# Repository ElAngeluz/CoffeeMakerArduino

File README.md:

# CoffeeMakerArduino
Hackear una cafetera simple para que se pueda conectar a Internet y de tal forma poder controlarla remotamente. Además la cafetera puede reportar su estado mediante una aplicacion android.

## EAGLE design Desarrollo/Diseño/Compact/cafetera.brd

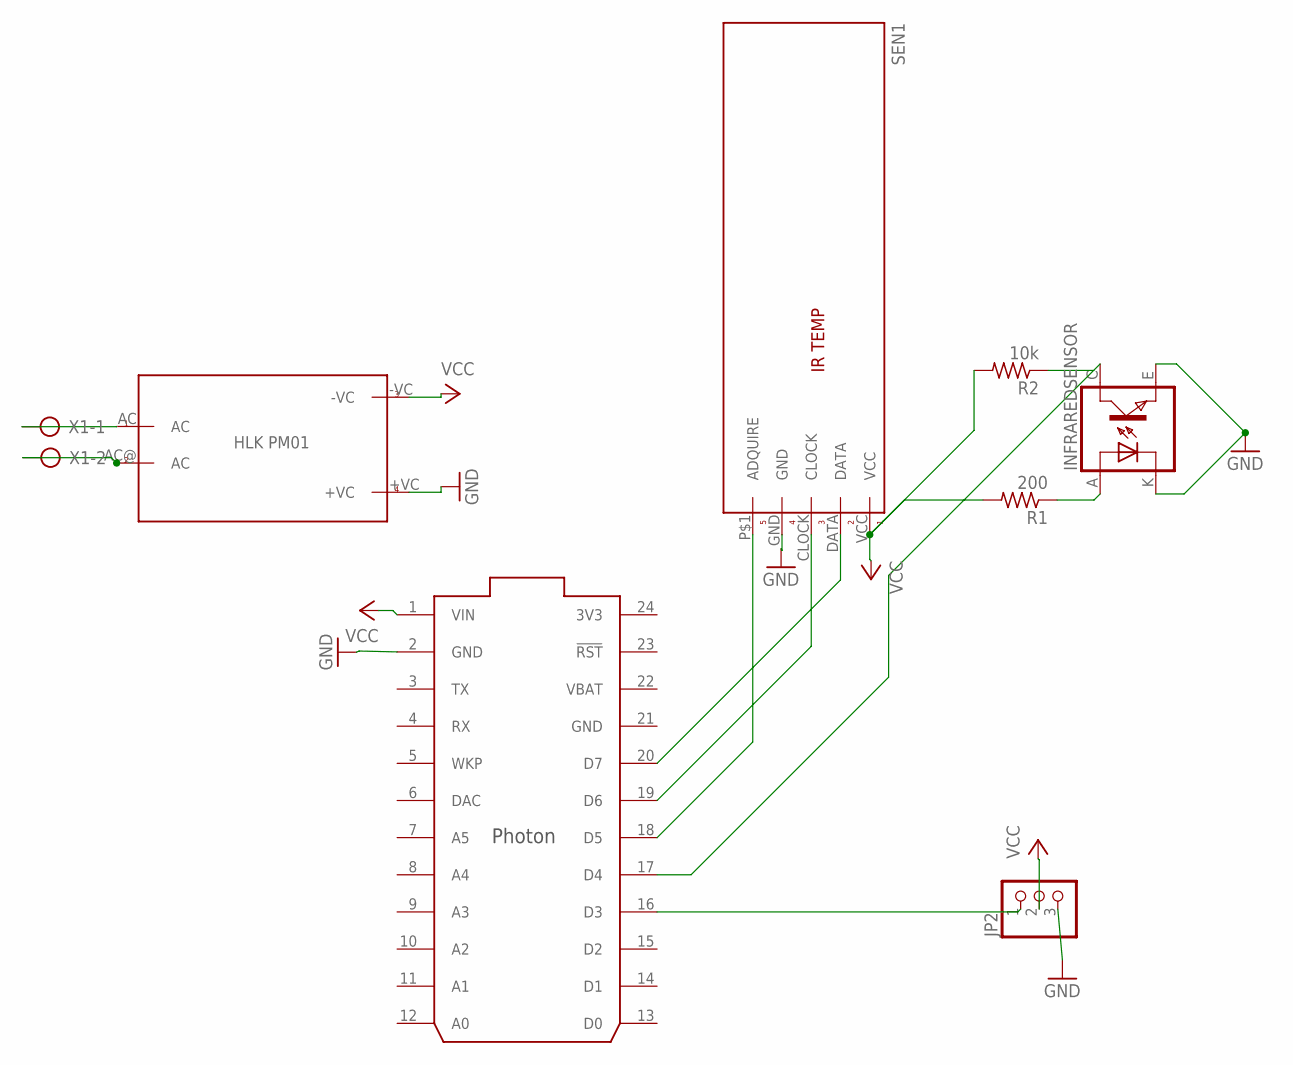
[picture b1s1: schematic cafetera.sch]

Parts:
INFRAREDSENSOR: TCRT5000
JP2: PINHD-1X3/90; 1X03/90
R1: 200; 0207/12
R2: 10k; 0207/12
SEN1: IRTEMP
TRANS1: HLKPM01
U$1: PHOTON_WITH_HEADERS; PHOTON
X1: AK500/2-H

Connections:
3V3: U$1.24 (3V3)
GND: INFRAREDSENSOR.E (EMITTER), INFRAREDSENSOR.K (CATHODE), JP2.3, SEN1.GND, TRANS1.+VC, U$1.2 (GND), U$1.21 (GND)
unnamed: INFRAREDSENSOR.A (ANODE), R1.1
unnamed: TRANS1.AC, X1.1
unnamed: R2.1, U$1.17 (D4)
unnamed: TRANS1.AC@ (AC), X1.2
unnamed: SEN1.DATA, U$1.20 (D7)
unnamed: SEN1.CLOCK, U$1.19 (D6)
unnamed: SEN1.P$1 (ADQUIRE), U$1.18 (D5)
unnamed: JP2.1, U$1.16 (D3)
VBAT: U$1.22 (VBAT)
VCC: JP2.2, R1.2, R2.2, SEN1.VCC, TRANS1.-VC, U$1.1 (VIN)

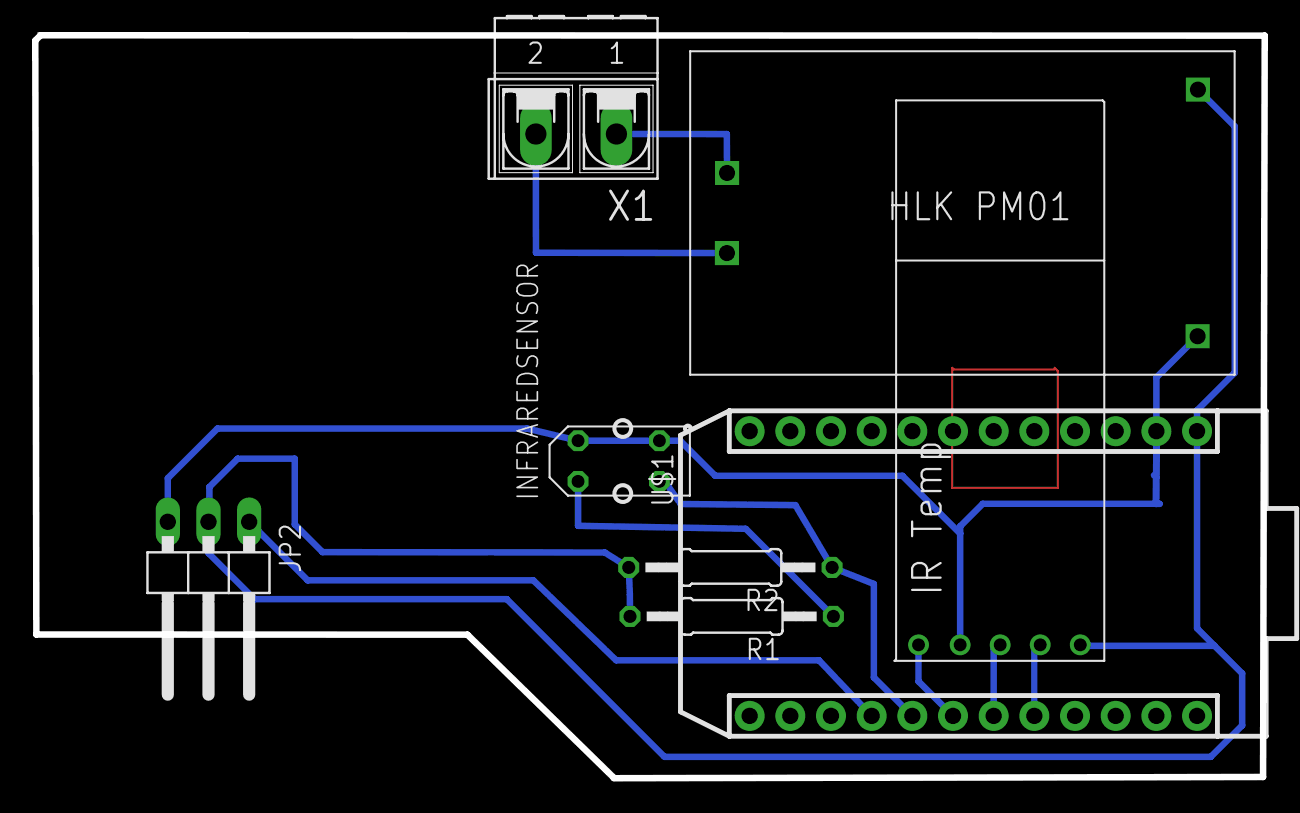
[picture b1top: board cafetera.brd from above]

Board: 2 copper layers, 76.8 x 46.4 mm, 8 parts (0 on the bottom side), 10 nets.

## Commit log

2016-01-18 README
    Proyecto 2 parcial Diseño
2016-01-25 Init commit.
2016-02-18 Agregacion de sensor de proximidad
    Add the sensor and the umbral funtion for management of the stated of
    de coffee maker
2016-02-18 Connect with thinkSpeak the proximity sensor
    Update the sensor in 15s to the ThinkSpeak
2016-02-21 add arduino and temperature with the get response
2016-02-22 working the coffee maker with multiple http request
2016-02-24 Add state machine for arduino
2016-02-26 add status for send and read http request with mix
2016-02-26 Add comments
2016-02-27 Repair somes bugs on Http request for the get and post data
2016-03-07 se cargan los proyectos en el repositorio
2016-03-27 primer commit
2016-03-31 libreria thingspeak
2016-04-06 modificando el archivo original
2016-04-06 Revert "modificando el archivo original"
    This reverts commit 9fa7eafbf75fbd22df87713e3c60819bbf6e731a.
2016-04-06 Revert "Revert "modificando el archivo original""
    This reverts commit 7f8cdadf218aab95e4d816dcc15974830f295c6e.
2016-04-06 archivo funcional
2016-05-03 codigo funcional
2016-05-03 se agrega los archivos necesarios para appinventor
2016-05-03 se cargan las imagenes para el app
2016-05-31 Commit android studios
    se cargan archivos para andriod studios
2016-05-31 terminado fase de diseño experimental
2016-06-19 se carga la funcion 1.1.1 de paho
    pero no compila con el apk, problemas con la funcion callback
2016-06-20 fixes some bugs
2016-06-20 codigo cafetera
2016-06-30 correcion de algunos errores y optimizaciones
2016-07-07 presentacion para show 8 / julio
2016-08-04 optimizacion de proyectos
    se eliminan proyectos que no se usan
2017-03-13 carga de esquematicos
2017-03-21 mejoras
2017-04-20 add procesos
